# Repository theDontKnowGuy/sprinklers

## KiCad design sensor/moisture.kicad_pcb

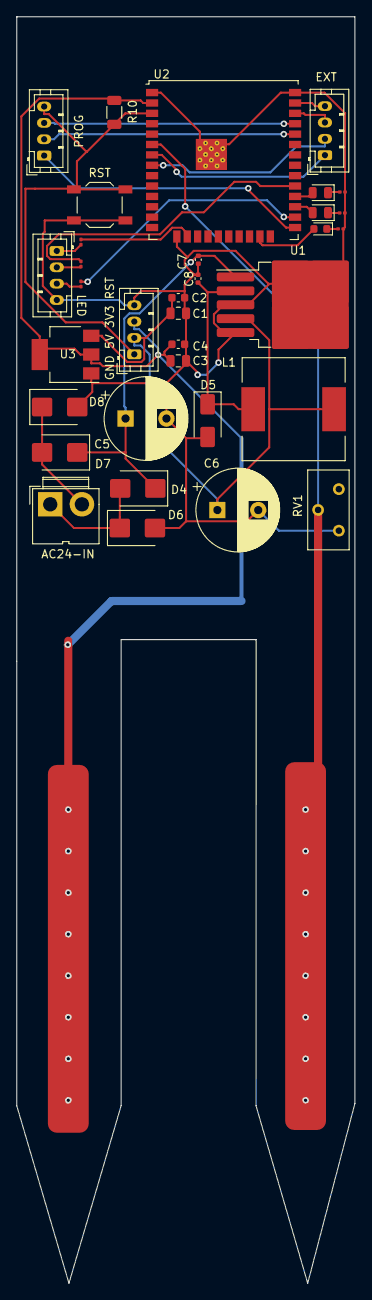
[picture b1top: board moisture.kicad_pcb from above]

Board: 2 copper layers, 41.4 x 154.9 mm, 34 parts (0 on the bottom side), 28 nets.

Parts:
AC24-IN1: Conn_01x02; JWT_A3963_1x02_P3.96mm_Vertical
C1, C3: 10uF; C_0805_2012Metric
C2, C4: 100nF; C_0603_1608Metric
C5, C6: C_Polarized; CP_Radial_D10.0mm_P5.00mm
C7, C8: 25V 1uF X5R ±10% 0402 Multilayer Ceramic Capacito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; C_0402_1005Metric
D1: LED; LED_0603_1608Metric
D2, D3: LED; LED_0805_2012Metric
D4, D6, D7, D8: 900mV@2A 30ns 2A 50V DO-214AA Diodes; D_SMB
D5: B140-E3; D_SMA
EXT1: Conn_01x04_Pin; JST_PH_B4B-PH-K_1x04_P2.00mm_Vertical
L1: L; L_12x12mm_H8mm
LED1: Conn_01x04_Pin; JST_PH_B4B-PH-K_1x04_P2.00mm_Vertical
POWER1: Conn_01x04_Pin; JST_PH_B4B-PH-K_1x04_P2.00mm_Vertical
PROG1: Conn_01x04_Pin; JST_PH_B4B-PH-K_1x04_P2.00mm_Vertical
R7, R8, R9, R11, R12, R13: 130; R_0201_0603Metric
R10: 10K; R_1206_3216Metric
RST_SW1: SW_SPST; SW_SPST_TL3342
RV1: R_Potentiometer_Small; Potentiometer_Bourns_3296Y_Vertical
U1: LM2596S-5; TO-263-5_TabPin3
U2: ESP32-WROOM-32U
U3: AP1117-33; SOT-223-3_TabPin2

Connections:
3V3: C3.1, C4.1, POWER1.3, R10.1, U2.2 (VDD), U3.2 (VO)
GRD: C1.2, C2.2, C3.2, C4.2, C5.2, C6.2, C7.1, C8.1, D5.2 (A), D6.2 (A), D8.2 (A), LED1.4, POWER1.4, R7.1, R8.1, R9.1, RST_SW1.2 (B), RV1.1, U1.3 (GND), U1.5 (~ON/OFF), U2.1 (GND), U2.15 (GND), U2.38 (GND), U2.39 (GND), U3.1 (GND)
unnamed: AC24-IN1.1, D4.2 (A), D6.1 (K)
unnamed: AC24-IN1.2, D7.2 (A), D8.1 (K)
unnamed: D1.2 (A), U2.23 (IO15)
unnamed: D1.1 (K), R9.2
unnamed: D2.2 (A), U2.27 (IO16)
unnamed: D2.1 (K), R8.2
unnamed: D3.2 (A), U2.28 (IO17)
unnamed: D3.1 (K), R7.2
unnamed: C5.1, C7.2, D4.1 (K), D7.1 (K), U1.1 (VIN)
unnamed: C8.2, D5.1 (K), L1.1, U1.2 (OUT)
unnamed: EXT1.1, U2.7 (IO35)
unnamed: EXT1.2, U2.8 (IO32)
unnamed: EXT1.3, U2.36 (IO22)
unnamed: EXT1.4, U2.37 (IO23)
unnamed: LED1.1, R11.1
unnamed: LED1.2, R12.1
unnamed: LED1.3, R13.1
unnamed: POWER1.1, PROG1.4, R10.2, RST_SW1.1 (A), U2.3 (EN)
unnamed: C1.1, C2.1, C6.1, L1.2, POWER1.2, U1.4 (FB), U3.3 (VI)
unnamed: PROG1.1, U2.25 (IO0)
unnamed: PROG1.2, U2.34 (RXD0/IO3)
unnamed: PROG1.3, U2.35 (TXD0/IO1)
unnamed: RV1.2, U2.6 (IO34)
unnamed: R13.2, U2.26 (IO4)
unnamed: R12.2, U2.29 (IO5)
unnamed: R11.2, U2.16 (IO13)

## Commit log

2023-10-12 orgenize schematic
2023-10-12 Replacing inductor
2023-10-13 tx/rx fix
2023-10-13 fix nets
2023-10-13 add moisture sensor
2023-11-04 V1.1.0 with notation
2023-11-06 applying fixed after review
2023-11-06 fix capacitor and connect q3
2023-11-06 fix EN net
2023-11-08 Rel V1.2
2023-11-09 fix footprint
